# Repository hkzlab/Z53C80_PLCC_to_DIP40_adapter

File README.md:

# Z53C80 PLCC to DIP40 adapter

## DISCLAIMER

Any use of this project is **under your own responsibility**.
You will be responsible of checking the correct construction and functionality of your board and the compatiblity of the chips You will insert into it.
By using this project You will agree that I cannot be held responsible if it will destroy any of your devices, damage your computer, burn down your house or whatever.

## Introduction

Building a Macintosh Plus clone, I noticed that 53C80 SCSI ICs in PLCC format are much more readily available than ones in DIP-40 package, required by the Mac Plus motherboard.

This adapter is just a pin-to-pin adapter that allows you to use a PLCC package in place of a DIP-40 one.

## Hardware

First of all, solder the ceramic capacitor, then the headers. My advice is to insert them into a DIP40 socket to hold them still, fit the PCB on top of them, then **snip off all the posts overlapping with where the PLCC socket would sit**.
Once that is done, solder the headers, and avoid adding too much solder to the stubs near the space for the PLCC socket.

Insert the PLCC socket on top of the board, apply flux liberally and solder every pin, paying particular attention not to short them to the nearby headers.

Done.

### Bill of Materials

| Component         | Qty | Type / Value                   |
| ----------------- | --- | ------------------------------ |
| 20 pin header     |  2  | Machined pin headers           |
| PLCC44 socket     |  1  | Through hole PLCC 44 pin socket|
| C1                |  1  | 100nF / 1206 / ceramic         |

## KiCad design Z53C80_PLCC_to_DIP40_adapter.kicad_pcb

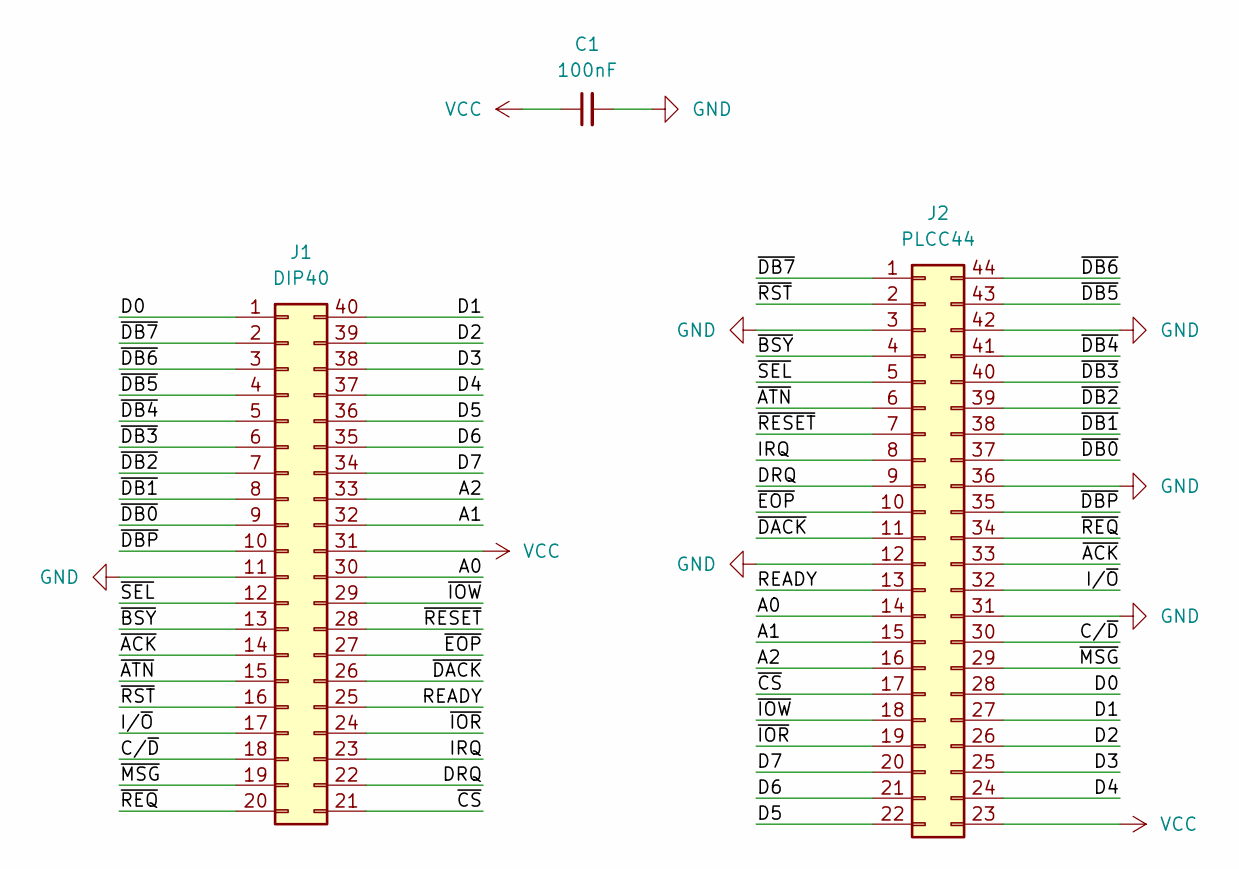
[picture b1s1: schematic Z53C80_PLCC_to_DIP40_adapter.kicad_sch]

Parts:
C1: 100nF; C_1206_3216Metric_Pad1.33x1.80mm_HandSolder
J1: DIP40; DIP-40_W15.24mm
J2: PLCC44; PLCC-44_THT-Socket

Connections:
/A0: J1.30, J2.14
/A1: J1.32, J2.15
/A2: J1.33, J2.16
/C/~D: J1.18, J2.30
/D0: J1.1, J2.28
/D1: J1.40, J2.27
/D2: J1.39, J2.26
/D3: J1.38, J2.25
/D4: J1.37, J2.24
/D5: J1.36, J2.22
/D6: J1.35, J2.21
/D7: J1.34, J2.20
/DRQ: J1.22, J2.9
/IRQ: J1.23, J2.8
/I/~O: J1.17, J2.32
/READY: J1.25, J2.13
/~ACK: J1.14, J2.33
/~ATN: J1.15, J2.6
/~BSY: J1.13, J2.4
/~CS: J1.21, J2.17
/~DACK: J1.26, J2.11
/~DB0: J1.9, J2.37
/~DB1: J1.8, J2.38
/~DB2: J1.7, J2.39
/~DB3: J1.6, J2.40
/~DB4: J1.5, J2.41
/~DB5: J1.4, J2.43
/~DB6: J1.3, J2.44
/~DB7: J1.2, J2.1
/~DBP: J1.10, J2.35
/~EOP: J1.27, J2.10
/~IOR: J1.24, J2.19
/~IOW: J1.29, J2.18
/~MSG: J1.19, J2.29
/~REQ: J1.20, J2.34
/~RESET: J1.28, J2.7
/~RST: J1.16, J2.2
/~SEL: J1.12, J2.5
GND: C1.2, J1.11, J2.3, J2.12, J2.31, J2.36, J2.42
VCC: C1.1, J1.31, J2.23

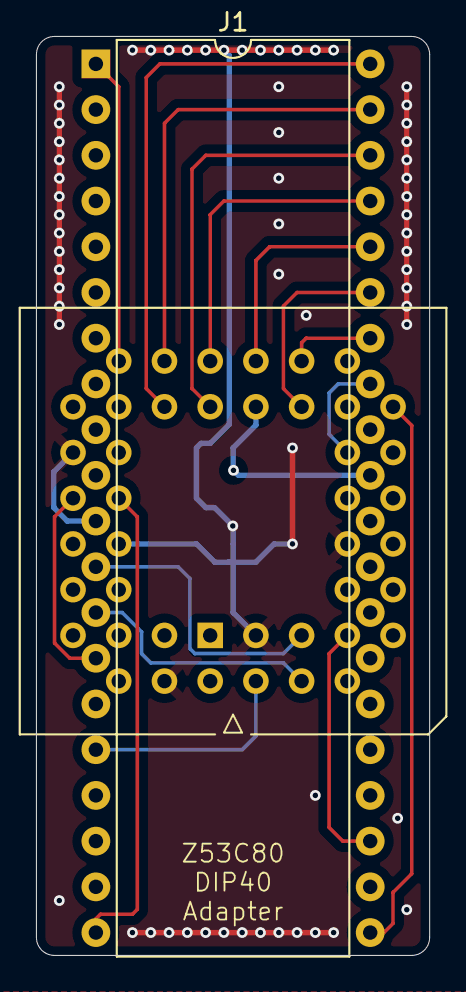
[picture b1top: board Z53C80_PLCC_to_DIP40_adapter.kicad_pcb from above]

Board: 4 copper layers, 21.8 x 51.1 mm, 3 parts (1 on the bottom side), 40 nets.

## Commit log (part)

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2024-09-25 Add basic adapter
2024-09-25 Update PCB
2024-09-25 Some more trace reorg
2024-09-25 Remove spurious trace
2024-09-25 Further adjustments to routing
2024-09-25 Further routing changes
2024-10-21 Add gerbers and schematics
2024-10-21 Update README and add pics
2025-01-26 Fix a typo
